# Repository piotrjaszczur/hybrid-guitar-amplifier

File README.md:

# hybrid-guitar-amplifier
Hybrid guitar amplifier project for the Design Laboratory course at AGH

This amplifier consists of valve preamplifier and solid state power amplifier.

Equalizer
The schematic for the equalizer was taken from the AVT186 kit. The values of the components were changed to provide three bands for the filters: 100Hz, 800Hz and 6400Hz.

MOSFET overdive effect
It was simple two stage amplifier to create distorted signal with a harsh clipping.

Channel select board
This board allowed to change the channels of the preamplifier and control the effects loop with 3 analog multiplexers. They were handled by the Atmega328p microcontroller. 

Power amplifier
The TDA7292 was used in the bridge tied load configuration to increase the power output in this stage.

Valve preamplifier
This circuit was based around 12AX7 valve. The double triode provided two gain stages in order to achieve overdriven signal.

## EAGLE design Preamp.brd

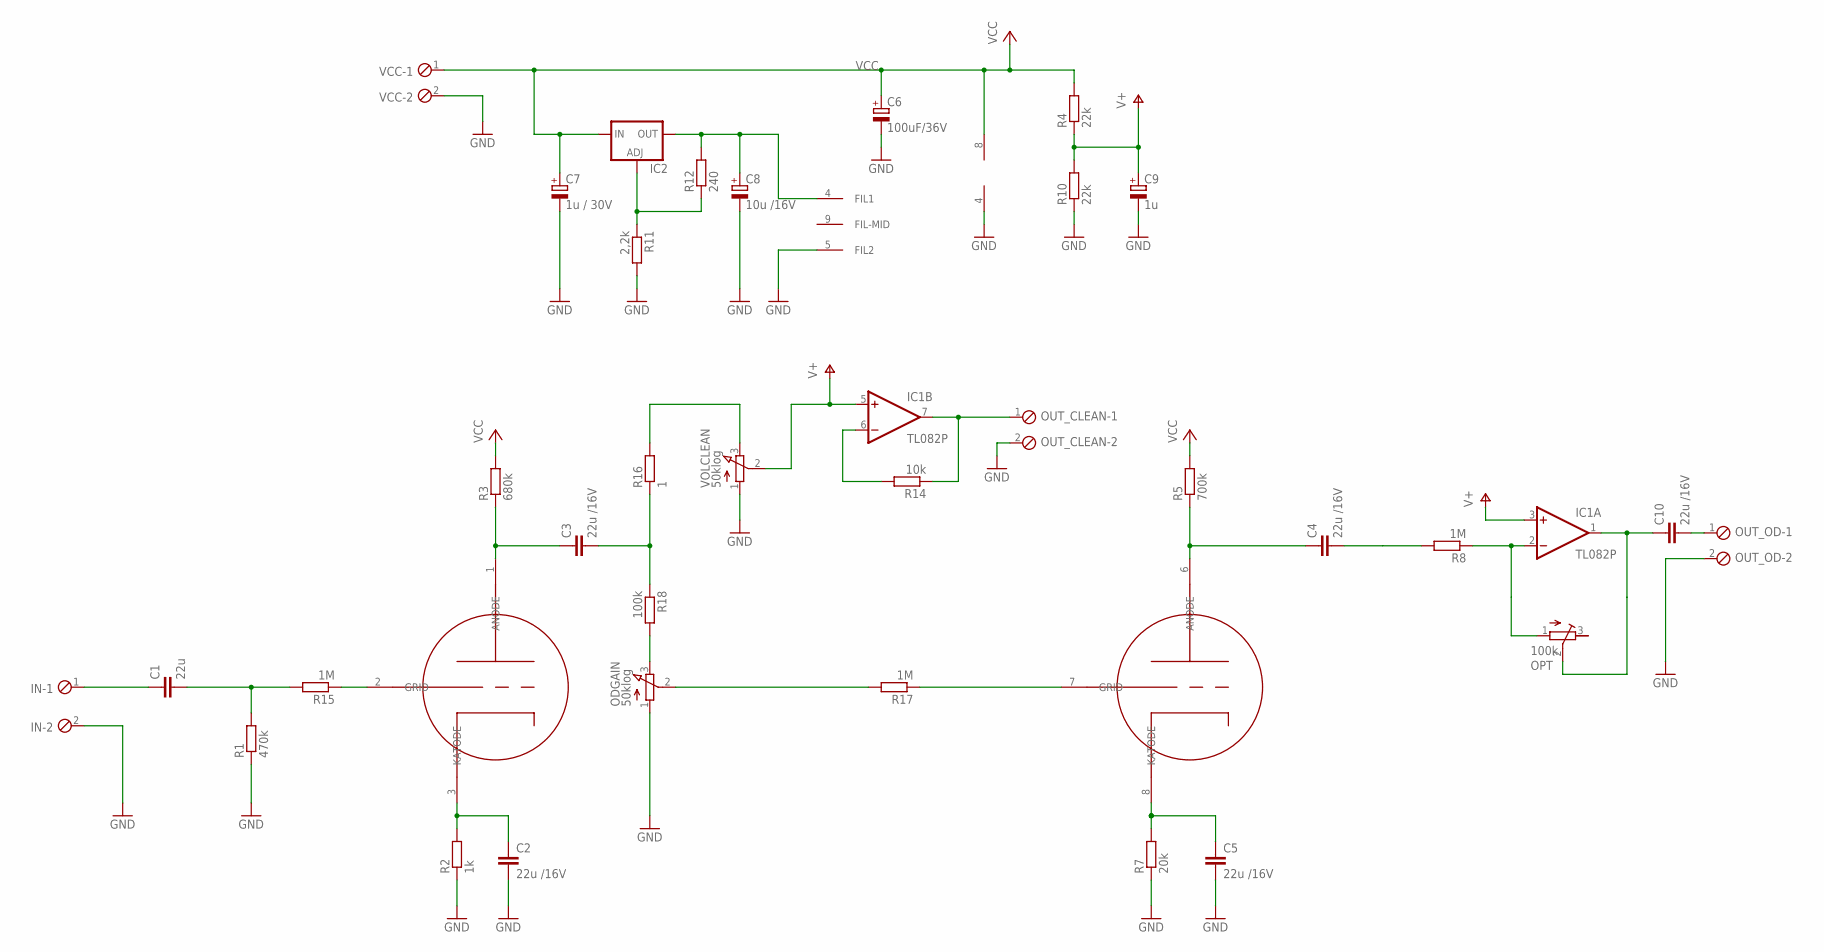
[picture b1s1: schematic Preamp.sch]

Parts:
C1: 22u; C050-030X075
C2, C3, C4, C5, C10: 22u /16V; C050-030X075
C6: 100uF/36V; E2,5-5
C7: 1u / 30V; E2,5-5
C8: 10u /16V; E2,5-5
C9: 1u; E2,5-5
IC1: TL082P; DIL08
IC2: LM317TS; 317TS
IN: MPT2; 2POL254
ODGAIN: 50klog; 3RP/1610N
OPT: 100k; RTRIM74W
OUT_CLEAN: MPT2; 2POL254
OUT_OD: MPT2; 2POL254
R1: 470k; 0207/12
R2: 1k; 0207/12
R3: 680k; 0207/12
R4, R10: 22k; 0207/12
R5: 700k; 0207/12
R7: 20k; 0207/10
R8, R15, R17: 1M; 0207/12
R11: 2,2k; 0207/12
R12: 240; 0207/12
R14: 10k; 0204/7
R16: 1; 0207/12
R18: 100k; 0207/12
U$1: 12AX7
VCC: MPT2; 2POL254
VOLCLEAN: 50klog; 3RP/1610N

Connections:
GND: C2.2, C5.2, C6.-, C7.-, C8.-, C9.-, IC1.4 (V-), IN.2, ODGAIN.1 (A), OUT_CLEAN.2, OUT_OD.2, R1.1, R2.1, R7.1, R10.1, R11.2, U$1.5 (FIL2), VCC.2, VOLCLEAN.1 (A)
unnamed: C1.2, R1.2, R15.2
unnamed: C2.1, R2.2, U$1.3 (KATODE)
unnamed: C5.1, R7.2, U$1.8 (KATODE)
unnamed: C3.1, R3.1, U$1.1 (ANODE)
unnamed: C3.2, R16.1, R18.1
unnamed: C4.1, R5.1, U$1.6 (ANODE)
unnamed: C4.2, R8.2
unnamed: C1.1, IN.1
unnamed: IC1.2 (-IN), OPT.1 (A), R8.1
unnamed: ODGAIN.2 (S), R17.2
unnamed: C10.1, IC1.1 (OUT), OPT.2 (S)
unnamed: IC1.7 (OUT), OUT_CLEAN.1, R14.1
unnamed: C8.+, IC2.2 (OUT), R12.2, U$1.4 (FIL1)
unnamed: R15.1, U$1.2 (GRID)
unnamed: IC2.1 (ADJ), R11.1, R12.1
unnamed: IC1.6 (-IN), R14.2
unnamed: R17.1, U$1.7 (GRID)
unnamed: R16.2, VOLCLEAN.3 (E)
unnamed: ODGAIN.3 (E), R18.2
unnamed: C10.2, OUT_OD.1
V+: C9.+, IC1.3 (+IN), IC1.5 (+IN), R4.1, R10.2, VOLCLEAN.2 (S)
VCC: C6.+, C7.+, IC1.8 (V+), IC2.3 (IN), R3.2, R4.2, R5.2, VCC.1

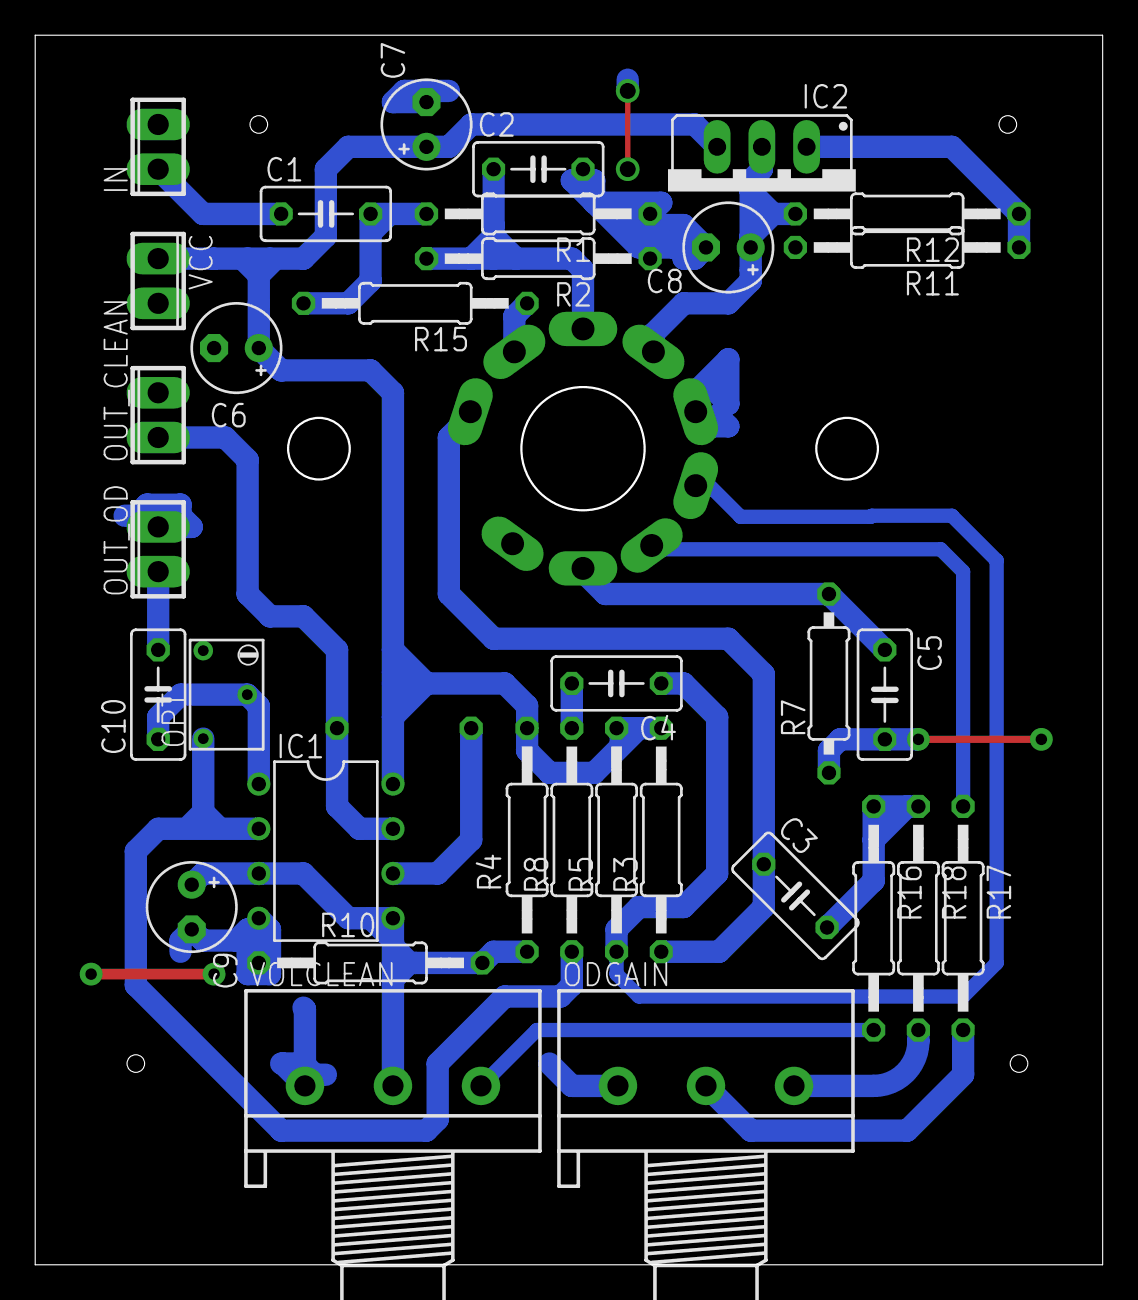
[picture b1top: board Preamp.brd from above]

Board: 2 copper layers, 60.5 x 69.7 mm, 35 parts (1 on the bottom side), 23 nets.

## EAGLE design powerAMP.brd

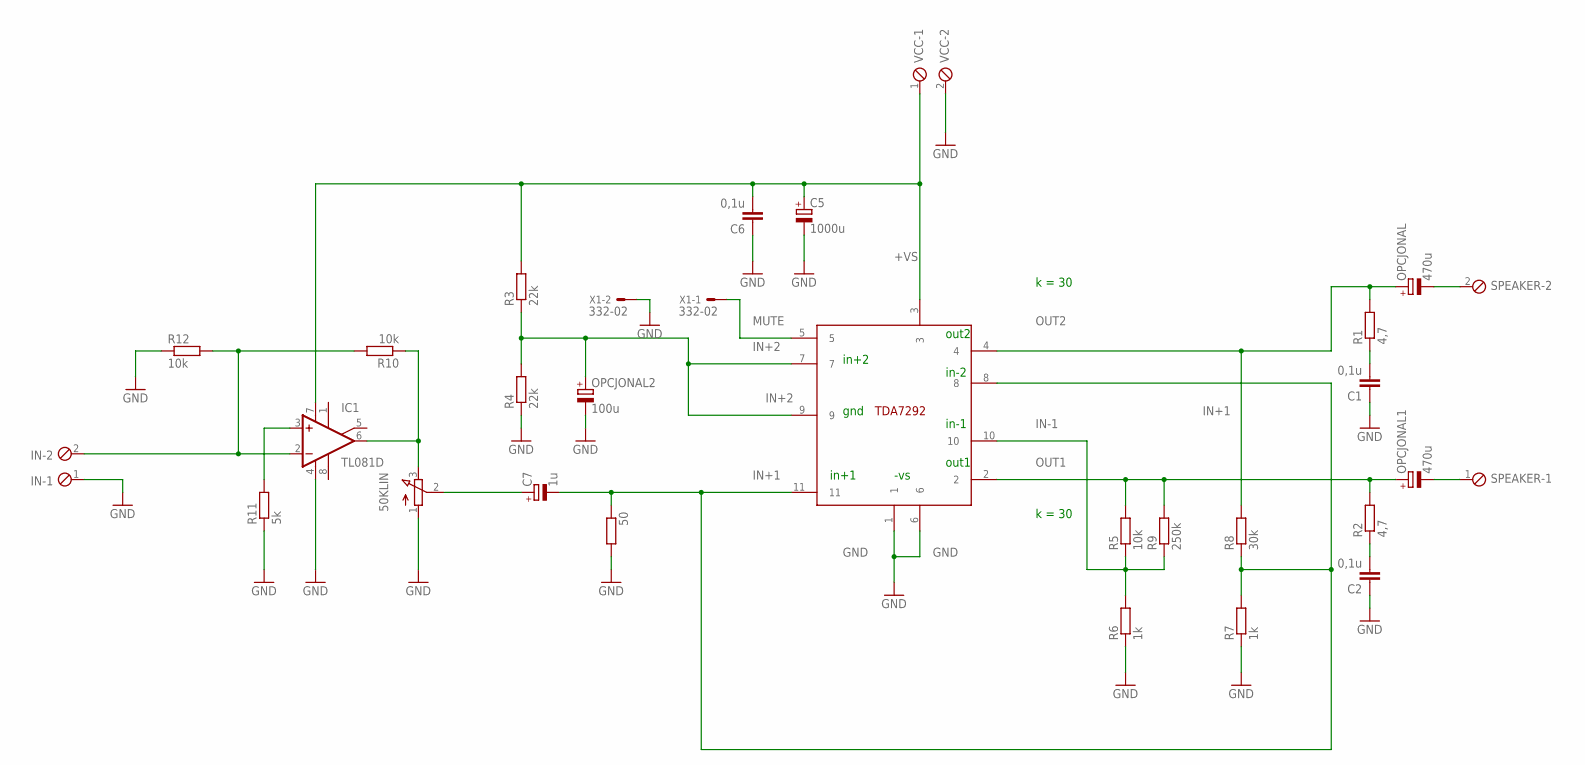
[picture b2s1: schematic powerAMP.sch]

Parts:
50: R-EU_M0805; M0805
50KLIN: 3RP/1610N
C1, C2, C6: 0,1u; C1206
C5: 1000u; E2,5-7
C7: 1u; E2,5-5
IC1: TL081D; SO08
IN: MPT2; 2POL254
OPCJONAL, OPCJONAL1: 470u; E2,5-7
OPCJONAL2: 100u; E2,5-7
R1, R2: 4,7; M0805
R3, R4: 22k; M0805
R5, R10, R12: 10k; M0805
R6, R7: 1k; M0805
R8: 30k; M0805
R9: 250k; M0805
R11: 5k; M0805
SPEAKER: MPT2; 2POL254
U$1: TDA7292TDA7292; MULTIWATT11
VCC: MPT2; 2POL254
X1: 332-02

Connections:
+VS: C5.+, C6.2, IC1.7 (V+), R3.2, U$1.3, VCC.1
GND: 50.2, 50KLIN.1 (A), C1.1, C2.1, C5.-, C6.1, IC1.4 (V-), IN.1, OPCJONAL2.-, R4.1, R6.1, R7.1, R11.1, R12.1, U$1.1, U$1.6, VCC.2, X1.2
IN+1: 50.1, C7.-, R7.2, R8.1, U$1.8, U$1.11
IN+2: OPCJONAL2.+, R3.1, R4.2, U$1.7, U$1.9
IN-1: R5.1, R6.2, R9.1, U$1.10
MUTE: U$1.5, X1.1
unnamed: C1.2, R1.1
unnamed: 50KLIN.3 (E), IC1.6 (OUT), R10.1
unnamed: 50KLIN.2 (S), C7.+
unnamed: C2.2, R2.1
unnamed: IC1.2 (-IN), IN.2, R10.2, R12.2
unnamed: IC1.3 (+IN), R11.2
OUT1: OPCJONAL1.+, R2.2, R5.2, R9.2, U$1.2
OUT2: OPCJONAL.+, R1.2, R8.2, U$1.4
SPK+: OPCJONAL1.-, SPEAKER.1
SPK-: OPCJONAL.-, SPEAKER.2

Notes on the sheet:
in-1
in+2
in-2
in+1
gnd
-vs
out1
out2
k = 30

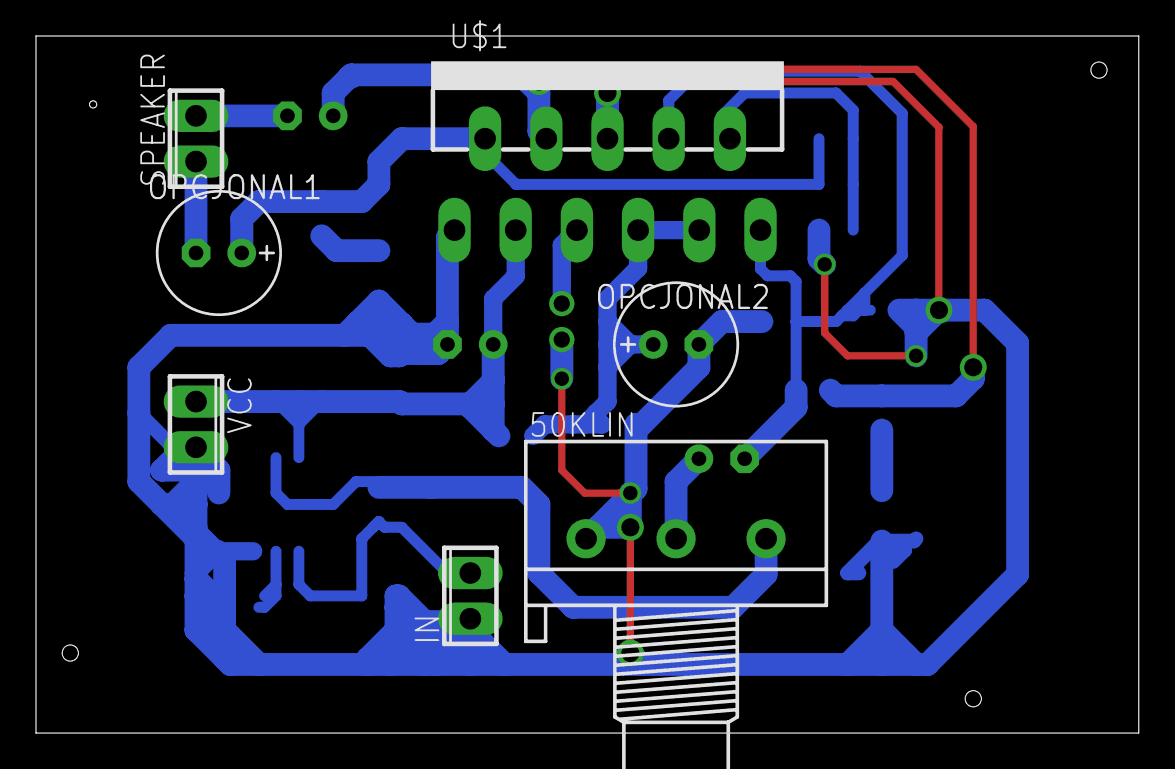
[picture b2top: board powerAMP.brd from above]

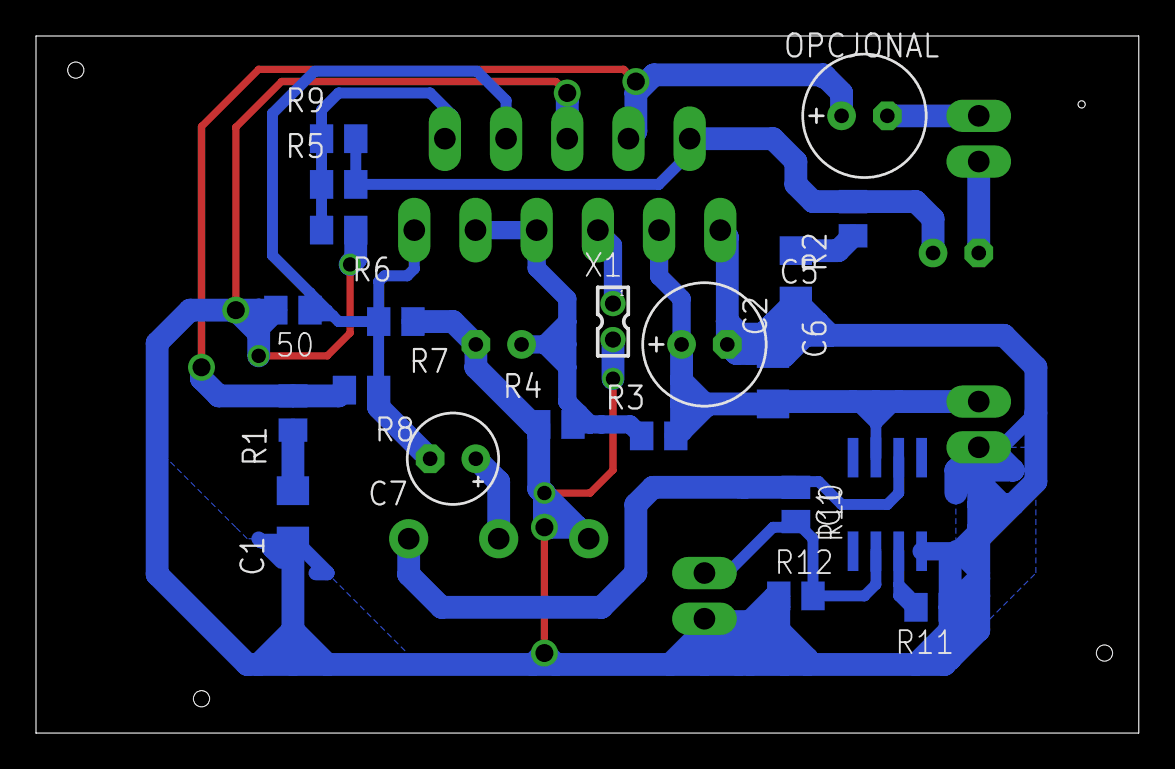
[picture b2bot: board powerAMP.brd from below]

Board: 2 copper layers, 61.3 x 38.7 mm, 28 parts (21 on the bottom side), 16 nets.

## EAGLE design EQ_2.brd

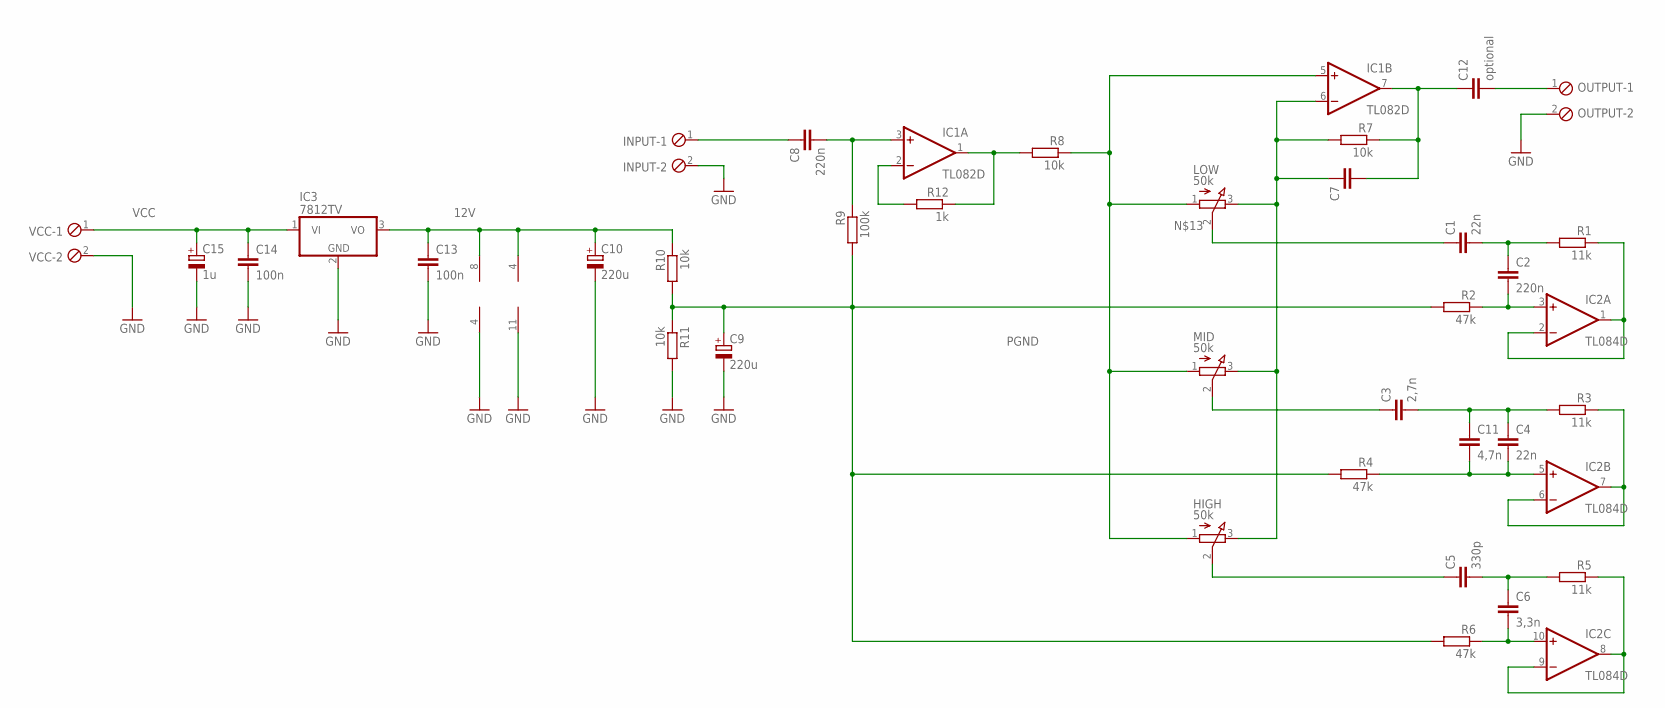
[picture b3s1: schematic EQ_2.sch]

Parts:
C1, C4: 22n; C1206
C2, C8: 220n; C1206
C3: 2,7n; C1206
C5: 330p; C1206
C6: 3,3n; C1206
C7: C-EUC1206; C1206
C9, C10: 220u; E2,5-5
C11: 4,7n; C1206
C12: optional; C1206
C13, C14: 100n; C1206
C15: 1u; E2,5-5
HIGH: 50k; 3RP/1610N
IC1: TL082D; SO08
IC2: TL084D; SO14
IC3: 7812TV; TO220V
INPUT: MPT2; 2POL254
LOW: 50k; 3RP/1610N
MID: 50k; 3RP/1610N
OUTPUT: MPT2; 2POL254
R1, R3, R5: 11k; R0805
R2, R4, R6: 47k; R0805
R7, R8, R10, R11: 10k; R0805
R9: 100k; R0805
R12: 1k; R0805
VCC: MPT2; 2POL254

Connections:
12V: C10.+, C13.1, IC1.8 (V+), IC2.4 (V+), IC3.3 (VO), R10.1
GND: C9.-, C10.-, C13.2, C14.2, C15.-, IC1.4 (V-), IC2.11 (V-), IC3.2 (GND), INPUT.2, OUTPUT.2, R11.2, VCC.2
unnamed: C2.2, IC2.3 (+IN), R2.1
unnamed: C1.2, C2.1, R1.2
unnamed: IC2.1 (OUT), IC2.2 (-IN), R1.1
unnamed: C3.2, C4.1, C11.1, R3.2
unnamed: C4.2, C11.2, IC2.5 (+IN), R4.1
unnamed: IC2.6 (-IN), IC2.7 (OUT), R3.1
unnamed: C5.2, C6.1, R5.2
unnamed: C6.2, IC2.10 (+IN), R6.1
unnamed: IC2.8 (OUT), IC2.9 (-IN), R5.1
unnamed: C7.2, C12.1, IC1.7 (OUT), R7.1
unnamed: C8.2, IC1.3 (+IN), R9.1
unnamed: C7.1, HIGH.3 (E), IC1.6 (-IN), LOW.3 (E), MID.3 (E), R7.2
unnamed: HIGH.1 (A), IC1.5 (+IN), LOW.1 (A), MID.1 (A), R8.1
unnamed: IC1.1 (OUT), R8.2, R12.1
unnamed: IC1.2 (-IN), R12.2
unnamed: C8.1, INPUT.1
unnamed: C5.1, HIGH.2 (S)
unnamed: C3.1, MID.2 (S)
unnamed: C1.1, LOW.2 (S)
unnamed: C12.2, OUTPUT.1
PGND: C9.+, R2.2, R4.2, R6.2, R9.2, R10.2, R11.1
VCC: C14.1, C15.+, IC3.1 (VI), VCC.1

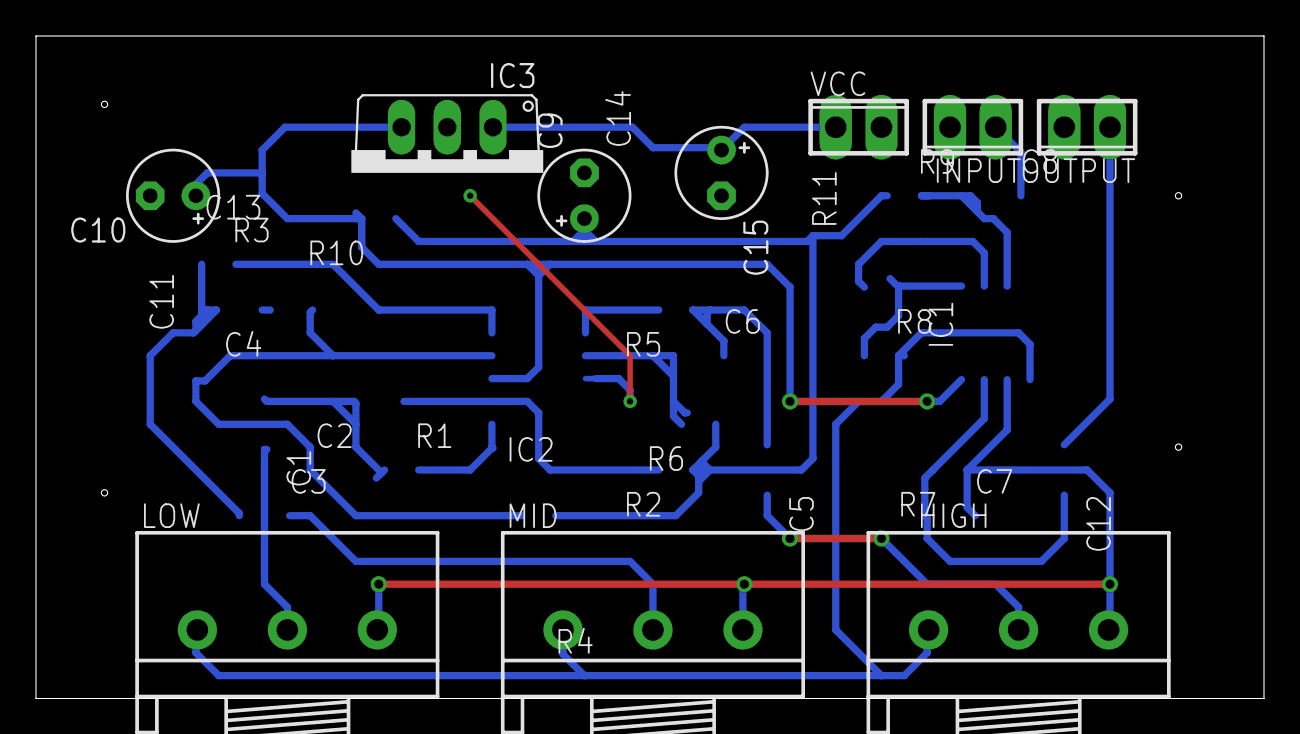
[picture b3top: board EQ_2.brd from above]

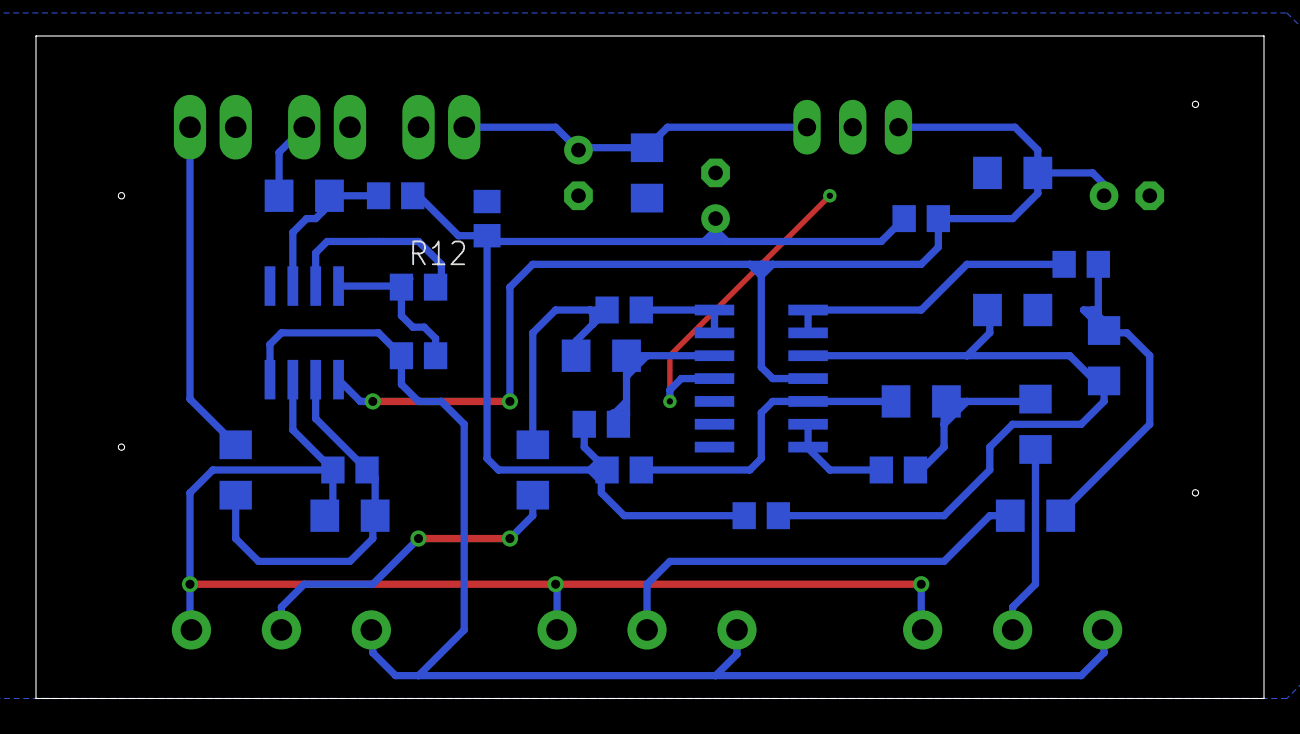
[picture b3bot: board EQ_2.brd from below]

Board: 2 copper layers, 68.2 x 36.8 mm, 36 parts (26 on the bottom side), 24 nets.

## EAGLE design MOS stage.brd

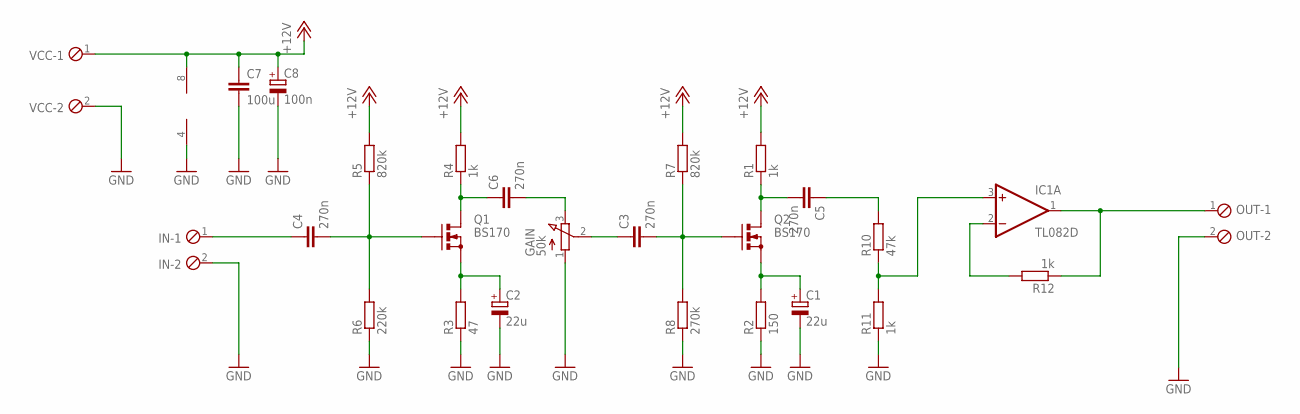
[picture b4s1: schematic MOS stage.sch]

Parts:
C1, C2: 22u; E2,5-5
C3, C4, C5, C6: 270n; C1206
C7: 100u; C1206
C8: 100n; E2,5-5
GAIN: 50k; 3RP/1610N
IC1: TL082D; SO08
IN: MPT2; 2POL254
OUT: MPT2; 2POL254
Q1, Q2: BS170; SOT54E
R1, R4, R11, R12: 1k; R0805
R2: 150; R0805
R3: 47; R0805
R5, R7: 820k; R0805
R6: 220k; R0805
R8: 270k; R0805
R10: 47k; R0805
VCC: MPT2; 2POL254

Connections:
+12V: C7.1, C8.+, IC1.8 (V+), R1.2, R4.2, R5.2, R7.2, VCC.1
GND: C1.-, C2.-, C7.2, C8.-, GAIN.1 (A), IC1.4 (V-), IN.2, OUT.2, R2.1, R3.1, R6.1, R8.1, R11.1, VCC.2
unnamed: C5.2, Q2.D, R1.1
unnamed: C3.2, Q2.G, R7.1, R8.2
unnamed: C1.+, Q2.S, R2.2
unnamed: C6.1, Q1.D, R4.1
unnamed: C2.+, Q1.S, R3.2
unnamed: C4.2, Q1.G, R5.1, R6.2
unnamed: C4.1, IN.1
unnamed: C5.1, R10.2
unnamed: C6.2, GAIN.3 (E)
unnamed: C3.1, GAIN.2 (S)
unnamed: IC1.3 (+IN), R10.1, R11.2
unnamed: IC1.1 (OUT), OUT.1, R12.1
unnamed: IC1.2 (-IN), R12.2

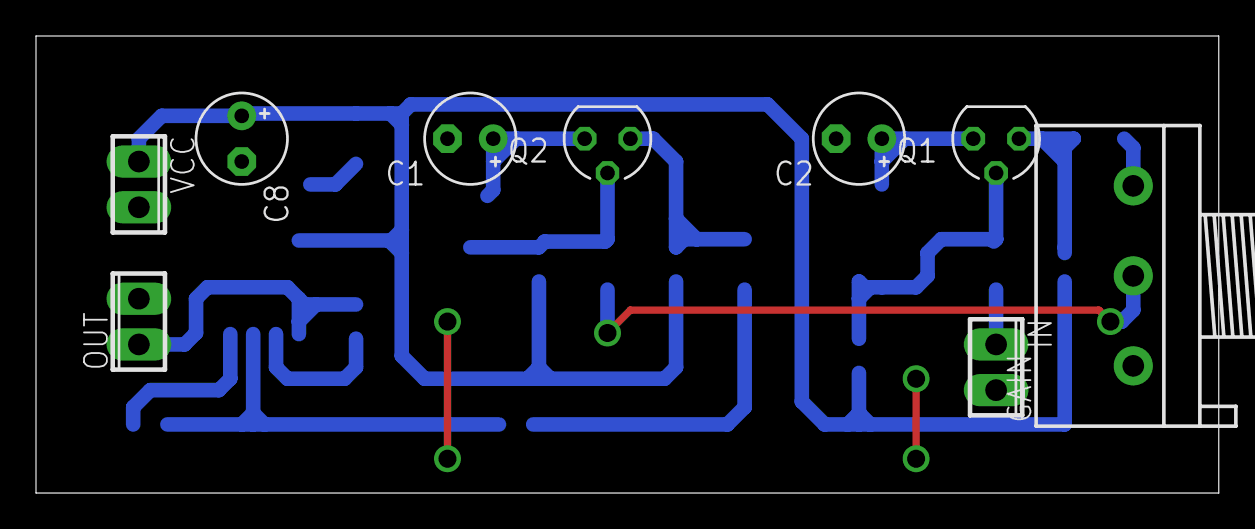
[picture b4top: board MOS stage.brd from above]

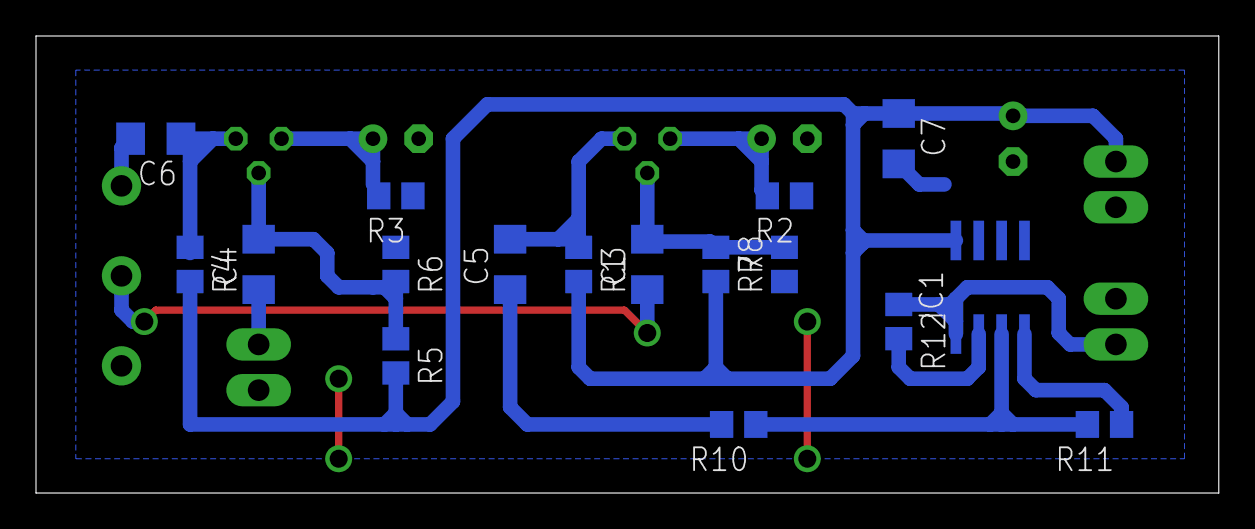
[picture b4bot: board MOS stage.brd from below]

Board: 2 copper layers, 65.7 x 25.4 mm, 26 parts (17 on the bottom side), 15 nets.

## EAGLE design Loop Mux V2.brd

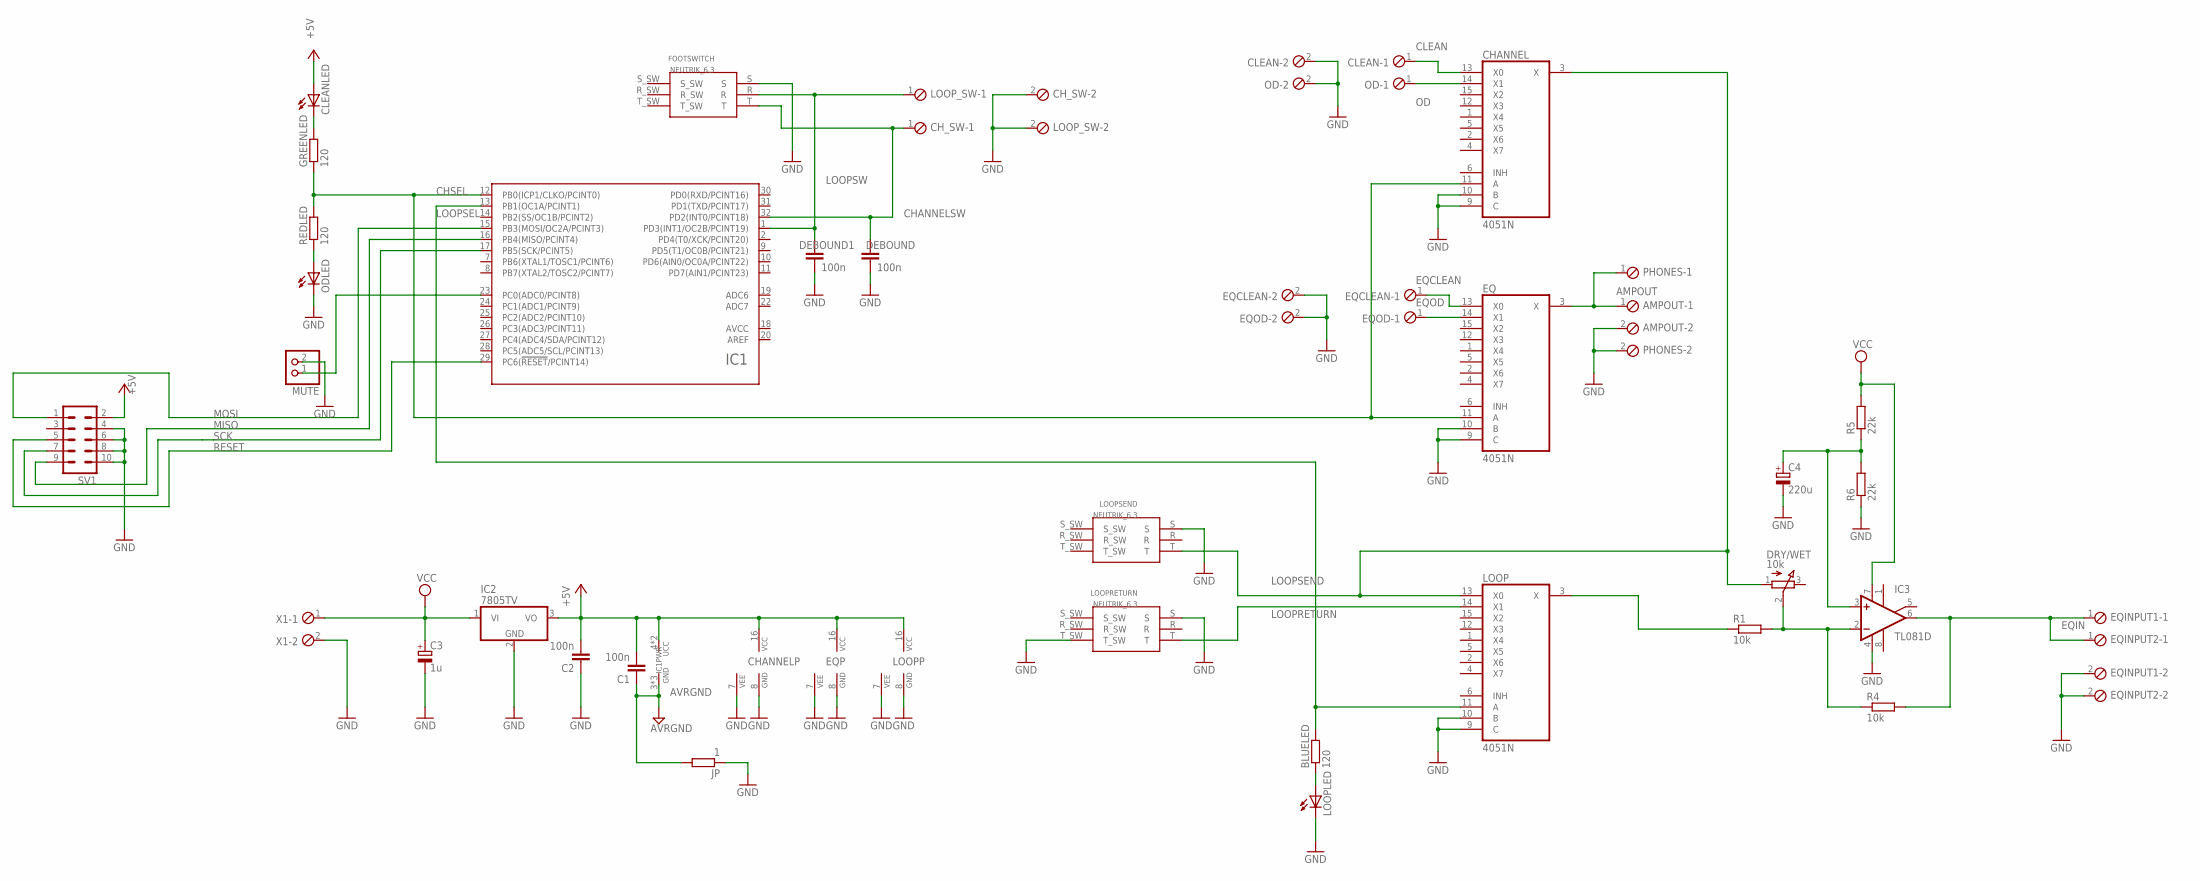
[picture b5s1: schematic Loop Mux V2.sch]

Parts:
AMPOUT: MPT2; 2POL254
BLUELED: 120; R0805
C1, C2: 100n; C1206
C3: 1u; E2-5
C4: 220u; E2,5-5
CHANNEL: 4051N; DIL16
CH_SW: MPT2; 2POL254
CLEAN: MPT2; 2POL254
CLEANLED: LED5MM
DEBOUND, DEBOUND1: 100n; C1206
DRY/WET: 10k; 3RP/1610N
EQ: 4051N; DIL16
EQCLEAN: MPT2; 2POL254
EQINPUT1, EQINPUT2: MPT2; 2POL254
EQOD: MPT2; 2POL254
FOOTSWITCH: NEUTRIK_6.3
GREENLED: 120; R0805
IC1: ATMEGA48/88/168/328-AU; TQFP32-08
IC2: 7805TV; TO220V
IC3: TL081D; SO08
JP: 1; R0805
LOOP: 4051N; DIL16
LOOPLED: LED5MM
LOOPRETURN: NEUTRIK_6.3
LOOPSEND: NEUTRIK_6.3
LOOP_SW: MPT2; 2POL254
MUTE: PINHD-1X2; 1X02
OD: MPT2; 2POL254
ODLED: LED5MM
PHONES: MPT2; 2POL254
R1, R4: 10k; R0805
R5, R6: 22k; R0805
REDLED: 120; R0805
SV1: MA05-2
X1: MPT2; 2POL254

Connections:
+5V: C1.2, C2.2, CHANNEL.16 (VCC), CLEANLED.A, EQ.16 (VCC), IC1.4 (UCC), IC1.6 (UCC), IC2.3 (VO), LOOP.16 (VCC), SV1.2
AMPOUT: AMPOUT.1, EQ.3 (X), PHONES.1
AVCC: IC1.18 (AVCC)
AVRGND: C1.1, IC1.3 (GND), IC1.5 (GND), IC1.21 (GND), JP.2
CHANNELSW: CH_SW.1, DEBOUND.1, FOOTSWITCH.T, IC1.32 (PD2(INT0/PCINT18))
CHSEL: CHANNEL.11 (A), EQ.11 (A), GREENLED.1, IC1.12 (PB0(ICP1/CLKO/PCINT0)), REDLED.2
CLEAN: CHANNEL.13 (X0), CLEAN.1
EQCLEAN: EQ.13 (X0), EQCLEAN.1
EQIN: EQINPUT1.1, EQINPUT2.1, IC3.6 (OUT), R4.2
EQOD: EQ.14 (X1), EQOD.1
GND: AMPOUT.2, C2.1, C3.-, C4.-, CHANNEL.7 (VEE), CHANNEL.8 (GND), CHANNEL.9 (C), CHANNEL.10 (B), CH_SW.2, CLEAN.2, DEBOUND.2, DEBOUND1.2, EQ.7 (VEE), EQ.8 (GND), EQ.9 (C), EQ.10 (B), EQCLEAN.2, EQINPUT1.2, EQINPUT2.2, EQOD.2, FOOTSWITCH.S, IC2.2 (GND), IC3.4 (V-), JP.1, LOOP.7 (VEE), LOOP.8 (GND), LOOP.9 (C), LOOP.10 (B), LOOPLED.K (C), LOOPRETURN.S, LOOPRETURN.T_SW, LOOPSEND.S, LOOP_SW.2, MUTE.2, OD.2, ODLED.K (C), PHONES.2, R6.1, SV1.4, SV1.6, SV1.8, SV1.10, X1.2
LOOPRETURN: LOOP.14 (X1), LOOPRETURN.T
LOOPSEL: BLUELED.2, IC1.13 (PB1(OC1A/PCINT1)), LOOP.11 (A)
LOOPSEND: CHANNEL.3 (X), DRY/WET.1 (A), LOOP.13 (X0), LOOPSEND.T
LOOPSW: DEBOUND1.1, FOOTSWITCH.R, IC1.1 (PD3(INT1/OC2B/PCINT19)), LOOP_SW.1
MISO: IC1.16 (PB4(MISO/PCINT4)), SV1.9
MOSI: IC1.15 (PB3(MOSI/OC2A/PCINT3)), SV1.1
unnamed: ODLED.A, REDLED.1
unnamed: IC1.23 (PC0(ADC0/PCINT8)), MUTE.1
unnamed: CLEANLED.K (C), GREENLED.2
unnamed: LOOP.3 (X), R1.1
unnamed: DRY/WET.2 (S), IC3.2 (-IN), R1.2, R4.1
unnamed: BLUELED.1, LOOPLED.A
unnamed: C4.+, IC3.3 (+IN), R5.1, R6.2
OD: CHANNEL.14 (X1), OD.1
RESET: IC1.29 (PC6(!RESET!/PCINT14)), SV1.5
SCK: IC1.17 (PB5(SCK/PCINT5)), SV1.7
VCC: C3.+, IC2.1 (VI), IC3.7 (V+), R5.2, X1.1

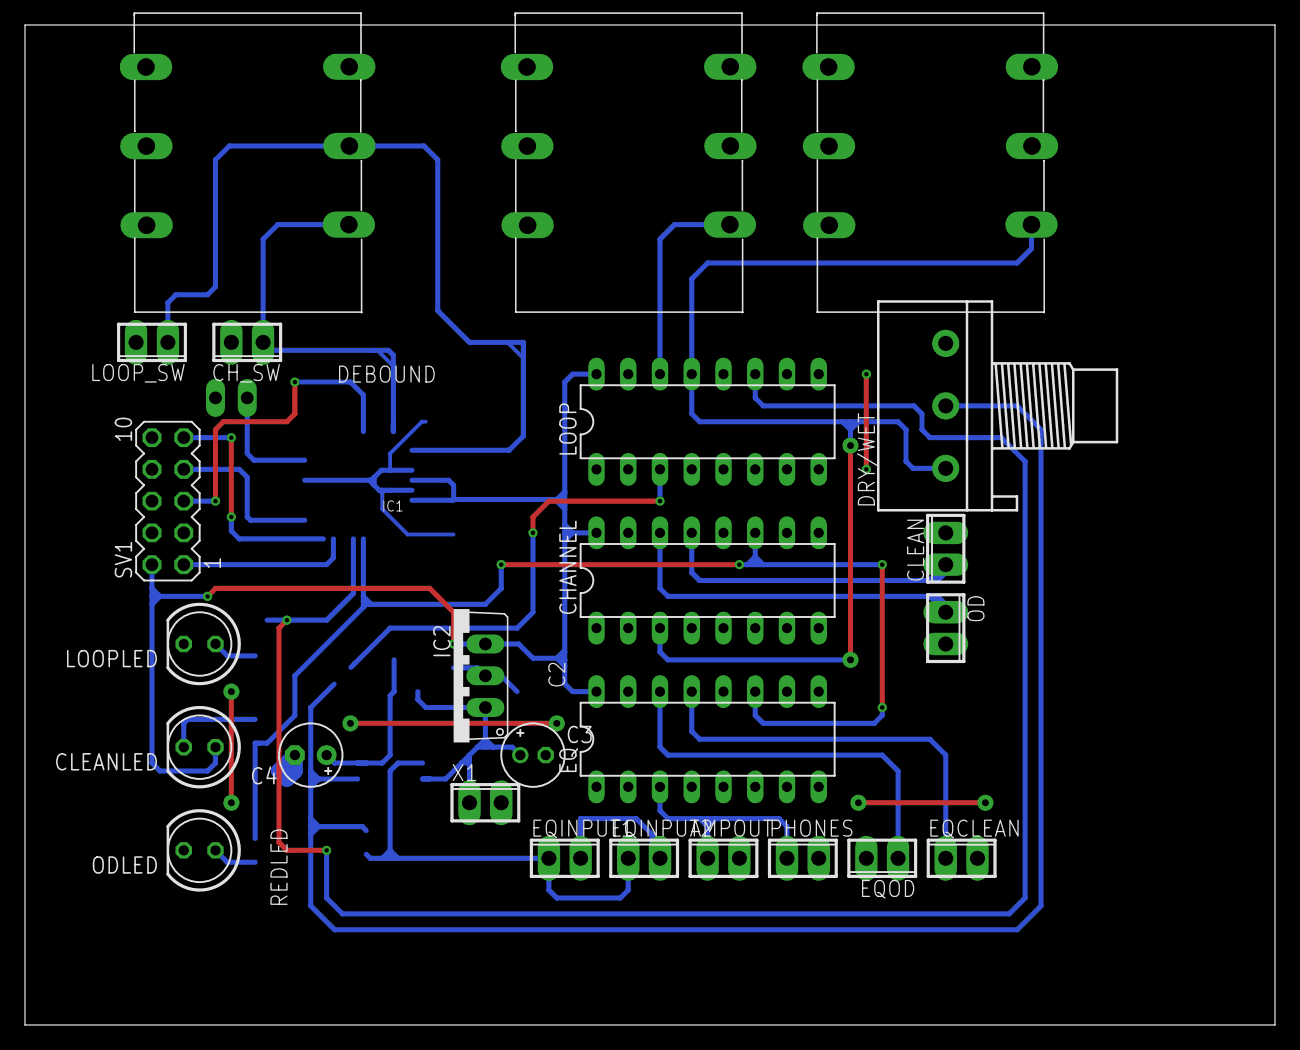
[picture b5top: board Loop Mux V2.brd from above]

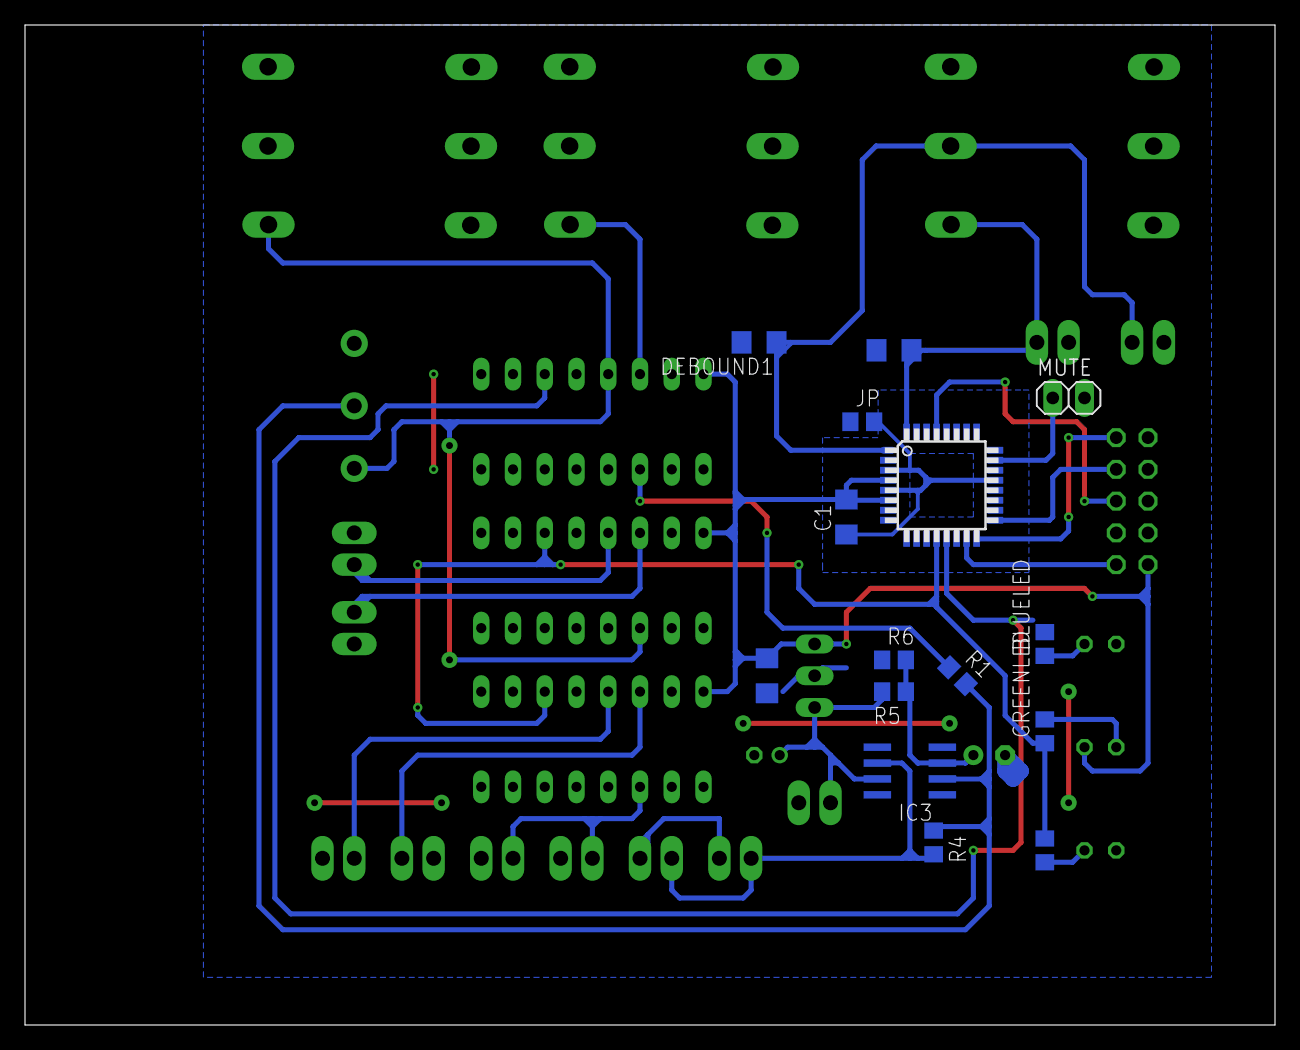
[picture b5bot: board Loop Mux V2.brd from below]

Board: 2 copper layers, 100.0 x 80.0 mm, 40 parts (15 on the bottom side), 27 nets.
